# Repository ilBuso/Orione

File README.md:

# Orione

Orione is a custom 60% mechanical keyboard powered by Raspberry Pi Pico.

## Table of Contents

- [About the Project](#about-the-project)
- [Key Features](#key-features)
- [Making It Your Own](#making-it-your-own)
- [What You'll Need](#what-youll-need)
  - [Hardware Components](#hardware-components)
  - [Software Tools](#software-tools)
- [The PCB](#the-pcb)
- [The Chassis](#the-chassis)
- [Project layout](#project-layout)
- [Video and Presentation](#video-and-presentation)
- [The Team](#the-team)

## About the Project

The need for a keyboard with a rotary encoder that could be customized without compromising on functionality sparked the creation of this project. When existing options fell short of meeting these requirements, Orione was born: a custom 60% mechanical keyboard powered by the Raspberry Pi Pico, featuring fully customizable firmware and a dual-layer system that packs maximum functionality into a minimal footprint.

Orione is built around the compact 60% keyboard layout, which strips away the function row and number pad to create a more ergonomic typing experience. At its heart is the Raspberry Pi Pico microcontroller, an affordable and reliable brain that handles everything from key presses to USB communication.

What makes Orione special is its programmable dual-layer system. Through a dedicated function key, you can access an entirely separate layer of key functions, meaning you don't lose any functionality despite the smaller form factor. It's like having two keyboards in one compact package.

## Key Features

The design philosophy behind Orione was simple: create something that feels personal and works exactly the way I want it to. Here's what that translated into:

The **60% layout** keeps everything within easy reach, no more stretching for distant keys or function rows. A **dual-layer system** accessed through a dedicated function key means I haven't sacrificed any functionality for compactness.

The **rotary encoder** handles volume control beautifully, with raise, lower, and mute functionality at your fingertips. There's also a **Caps Lock LED indicator** for quick visual feedback.

For switches are for the most part **Gateron Yellow switches** that provide smooth linear action for most keys, while **Gateron Blue switches** offer tactile feedback on select keys where I wanted that extra confirmation.

Most importantly, the firmware is **fully customizable**. Every key can be remapped, every function can be changed. The Raspberry Pi Pico makes this possible, and the open-source nature of the project means you're never locked into my choices.

## Making It Your Own

One of Orione's defining features is how easily you can make it yours. The firmware is completely open and modifiable. Want to change what a key does? Remap the function layer? It's all possible:

Start by editing the keymap configuration files to match your preferences. Once you're happy with your changes, recompile the firmware and flash it to your Raspberry Pi Pico. That's it, you've got a personalized keyboard that works exactly the way you want it to.

## What You'll Need

### Hardware Components

Building Orione requires a carefully selected set of components. You'll need a **Raspberry Pi Pico** as the microcontroller, it's the brain of the operation. The **rotary encoder** provides that tactile volume control I was after, while a **LED** serves as the Caps Lock indicator.s

For the switches, you'll need **62 mechanical switches** total. You'll also need a matching set of **62 keycaps** and **62 diodes** for the key matrix.

Finally, there's the **custom PCB** that I designed specifically for this project, bringing all these components together in a compact and functional layout.

### Software Tools

The development environment revolves around **VS Code**, which I used for writing and debugging the firmware. For the PCB design, **KiCad** handled both the schematics and the layout. The chassis and 3D components were modeled in **Blender**.

On the firmware side, the project uses the **Raspberry Pi Pico C/C++ SDK**, following the official _Getting Started guide_ will get you set up properly. The **TinyUSB Library** is crucial here, as it enables USB HID communication between the Pico and your computer through the micro USB port, making the keyboard actually function as, well, a keyboard.

## The PCB

## The Chassis

## Project layout

```
/
├───datasheets
|   └───...
├───firmware
│   ├───config
│   └───src
│       ├───init
│       │   ├───init.h
│       │   └───init.c
│       ├───interrupts
│       │   ├───interrupts.h
│       │   └───interrupts.c
│       ├───matrix
│       │   ├───keymap
│       │   │   ├───keymap.h
│       │   │   └───keymap.c
│       │   └───scan_rows
│       │       ├───scan_rows.h
│       │       └───scan_rows.c
│       ├───rotary_encoder
│       │   ├───rotary_encoder.h
│       │   └───rotary_encoder.c
│       └───usb
│           ├───usb_callbacks
│           │  ├───usb_callbacks.h
│           │  └───usb_callbacks.c
│           └───usb_descriptors
│              ├───usb_descriptors.h
│              └───usb_descriptors.c
├───pcb
│   └───...
└───chassis
    └───...
```

## Video and Presentation

[Video](https://youtu.be/jeuJEti2THU)

[Presentation](assets/Orione.pdf)

## The Team

In the team we collaborated closely with eachother, both in presence and through Github.

|Name|Github handle|
|---|---|
|Alessandro Busola| [@ilBuso](https://github.com/ilBuso)|
|Giulio Pimenoff Verdolin|[@Giuliopime](https://github.com/Giuliopime)|
|Michele Pezzo|[@MichelePZZ](https://github.com/MichelePZZ)|
|Daniel Biz|[@BizDaniel](https://github.com/BizDaniel)|

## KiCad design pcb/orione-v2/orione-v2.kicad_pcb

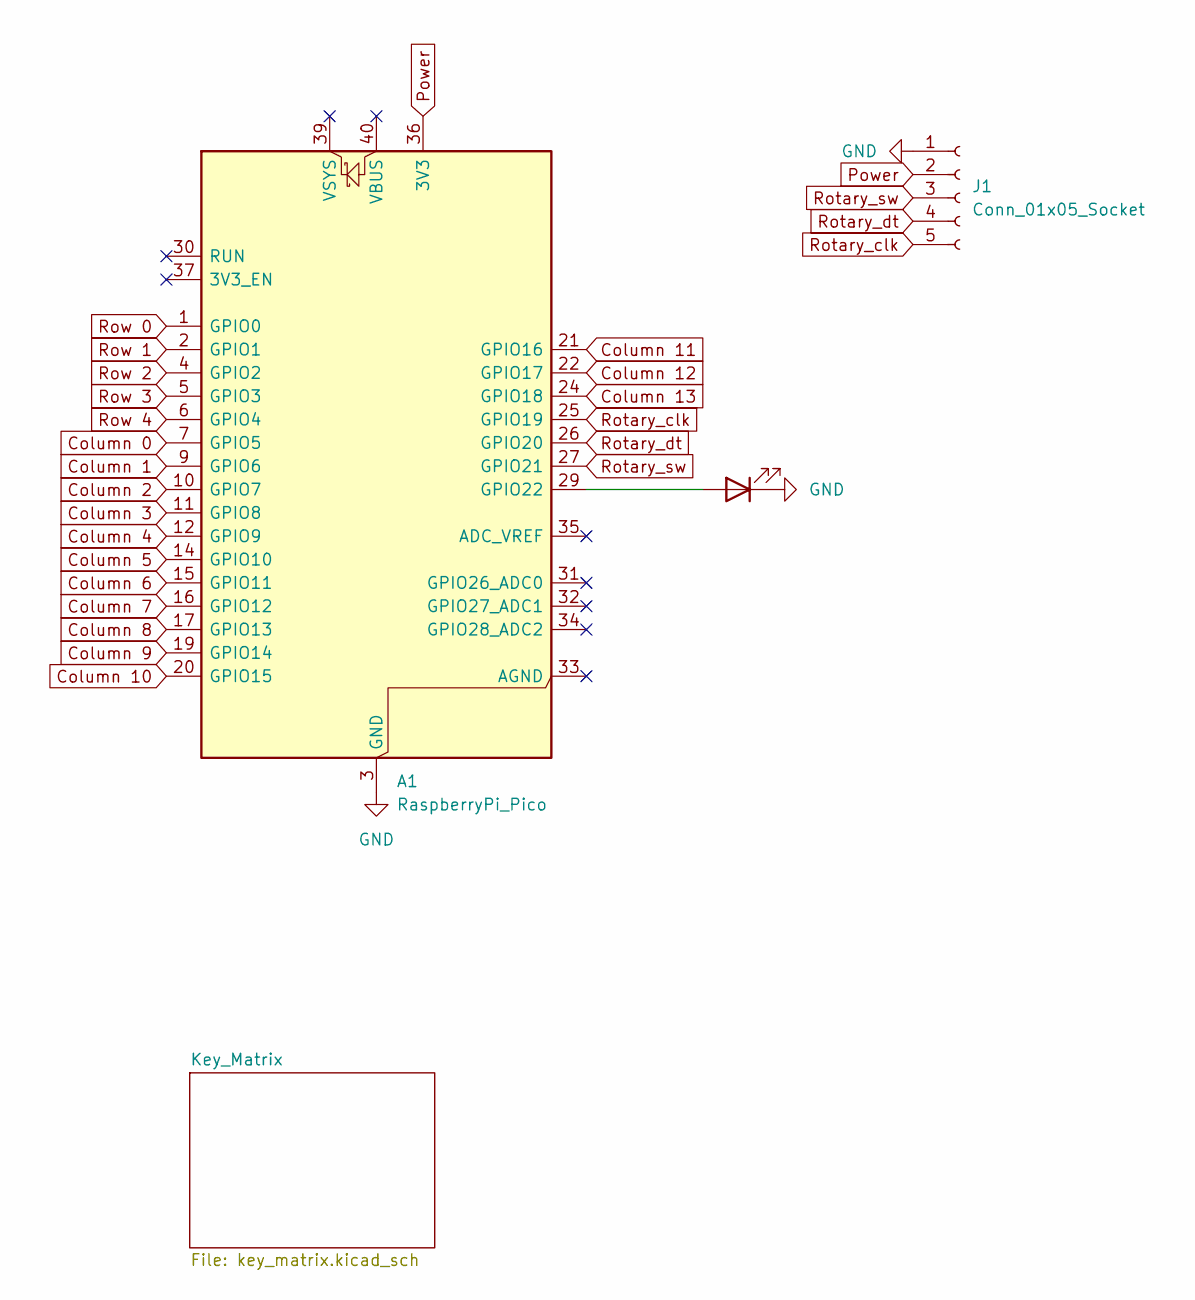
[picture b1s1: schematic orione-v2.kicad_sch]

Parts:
A1: RaspberryPi_Pico; RaspberryPi_Pico_Common_Unspecified
D63: LED; LED_D5.0mm
J1: Conn_01x05_Socket; PinSocket_1x05_P2.54mm_Vertical

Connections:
Column 0: A1.7 (GPIO5); also elsewhere on the board
Column 1: A1.9 (GPIO6); also elsewhere on the board
Column 2: A1.10 (GPIO7); also elsewhere on the board
Column 3: A1.11 (GPIO8); also elsewhere on the board
Column 4: A1.12 (GPIO9); also elsewhere on the board
Column 5: A1.14 (GPIO10); also elsewhere on the board
Column 6: A1.15 (GPIO11); also elsewhere on the board
Column 7: A1.16 (GPIO12); also elsewhere on the board
Column 8: A1.17 (GPIO13); also elsewhere on the board
Column 9: A1.19 (GPIO14); also elsewhere on the board
Column 10: A1.20 (GPIO15); also elsewhere on the board
Column 11: A1.21 (GPIO16); also elsewhere on the board
Column 12: A1.22 (GPIO17); also elsewhere on the board
Column 13: A1.24 (GPIO18); also elsewhere on the board
GND: A1.3 (GND), A1.8 (GND), A1.13 (GND), A1.18 (GND), A1.23 (GND), A1.28 (GND), A1.38 (GND), D63.1 (K), J1.1
unnamed: A1.29 (GPIO22), D63.2 (A)
Power: A1.36 (3V3), J1.2
Rotary_clk: A1.25 (GPIO19), J1.5
Rotary_dt: A1.26 (GPIO20), J1.4
Rotary_sw: A1.27 (GPIO21), J1.3
Row 0: A1.1 (GPIO0); also elsewhere on the board
Row 1: A1.2 (GPIO1); also elsewhere on the board
Row 2: A1.4 (GPIO2); also elsewhere on the board
Row 3: A1.5 (GPIO3); also elsewhere on the board
Row 4: A1.6 (GPIO4); also elsewhere on the board

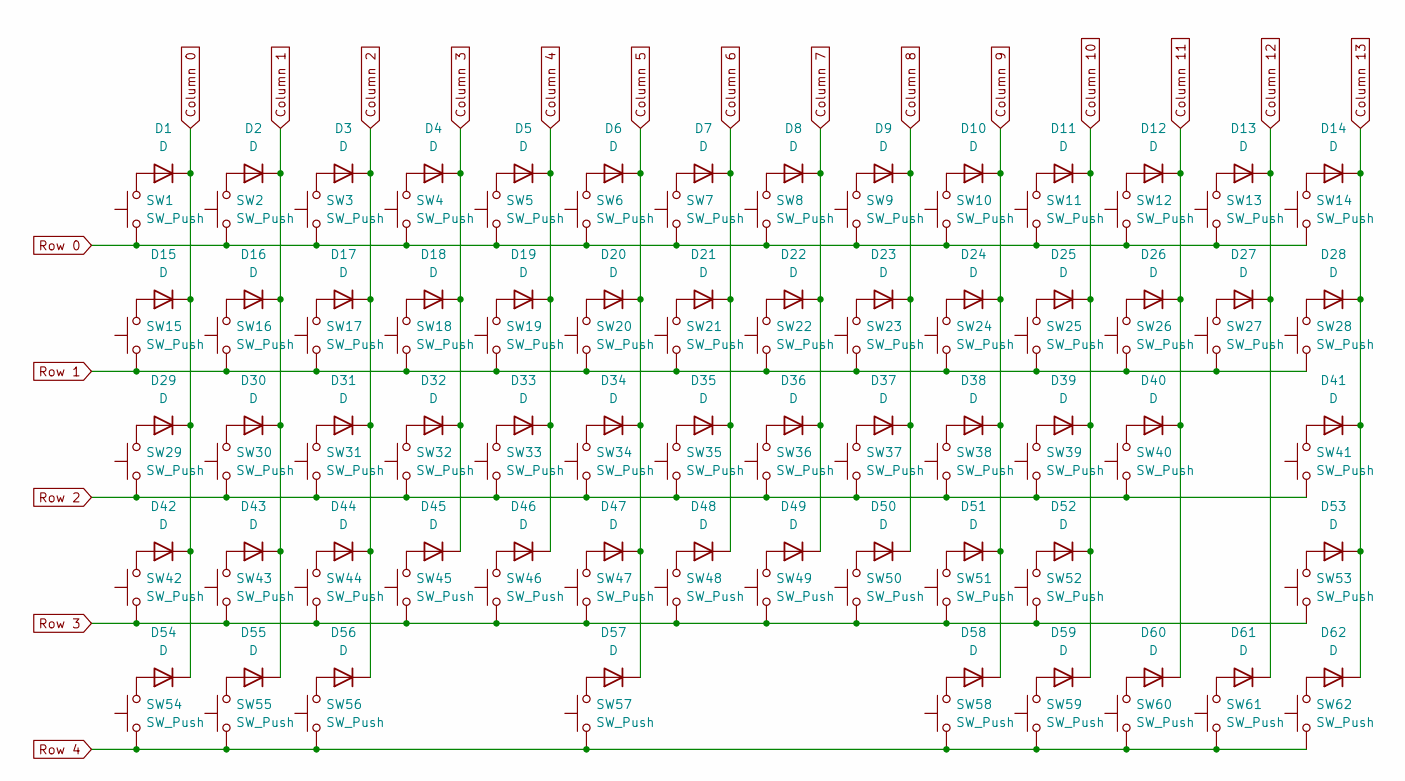
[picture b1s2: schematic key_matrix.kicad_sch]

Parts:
D1, D2, D3, D4, D5, D6, D7, D8, D9, D10, D11, D12, D13, D14, D15, D16, D17, D18, D19, D20, D21, D22, D23, D24, D25, D26, D27, D28, D29, D30, D31, D32, D33, D34, D35, D36, D37, D38, D39, D40, D41, D42, D43, D44, D45, D46, D47, D48, D49, D50, D51, D52, D53, D54, D55, D56, D57, D58, D59, D60, D61, D62: D; D_A-405_P7.62mm_Horizontal
SW1, SW2, SW3, SW4, SW5, SW6, SW7, SW8, SW9, SW10, SW11, SW12, SW13, SW16, SW17, SW18, SW19, SW20, SW21, SW22, SW23, SW24, SW25, SW26, SW27, SW30, SW31, SW32, SW33, SW34, SW35, SW36, SW37, SW38, SW39, SW40, SW43, SW44, SW45, SW46, SW47, SW48, SW49, SW50, SW51, SW52, SW58, SW59, SW60, SW61, SW62: SW_Push; SW_Cherry_MX_1.00u_PCB
SW14: SW_Push; SW_Cherry_MX_2.00u_PCB
SW15, SW28: SW_Push; SW_Cherry_MX_1.50u_PCB
SW29: SW_Push; SW_Cherry_MX_1.75u_PCB
SW41, SW42: SW_Push; SW_Cherry_MX_2.25u_PCB
SW53: SW_Push; SW_Cherry_MX_2.75u_PCB
SW54, SW55, SW56: SW_Push; SW_Cherry_MX_1.25u_PCB
SW57: SW_Push; SW_Cherry_MX_6.25u_PCB

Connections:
Column 0: D1.1 (K), D15.1 (K), D29.1 (K), D42.1 (K), D54.1 (K); also elsewhere on the board
Column 1: D2.1 (K), D16.1 (K), D30.1 (K), D43.1 (K), D55.1 (K); also elsewhere on the board
Column 2: D3.1 (K), D17.1 (K), D31.1 (K), D44.1 (K), D56.1 (K); also elsewhere on the board
Column 3: D4.1 (K), D18.1 (K), D32.1 (K), D45.1 (K); also elsewhere on the board
Column 4: D5.1 (K), D19.1 (K), D33.1 (K), D46.1 (K); also elsewhere on the board
Column 5: D6.1 (K), D20.1 (K), D34.1 (K), D47.1 (K), D57.1 (K); also elsewhere on the board
Column 6: D7.1 (K), D21.1 (K), D35.1 (K), D48.1 (K); also elsewhere on the board
Column 7: D8.1 (K), D22.1 (K), D36.1 (K), D49.1 (K); also elsewhere on the board
Column 8: D9.1 (K), D23.1 (K), D37.1 (K), D50.1 (K); also elsewhere on the board
Column 9: D10.1 (K), D24.1 (K), D38.1 (K), D51.1 (K), D58.1 (K); also elsewhere on the board
Column 10: D11.1 (K), D25.1 (K), D39.1 (K), D52.1 (K), D59.1 (K); also elsewhere on the board
Column 11: D12.1 (K), D26.1 (K), D40.1 (K), D60.1 (K); also elsewhere on the board
Column 12: D13.1 (K), D27.1 (K), D61.1 (K); also elsewhere on the board
Column 13: D14.1 (K), D28.1 (K), D41.1 (K), D53.1 (K), D62.1 (K); also elsewhere on the board
unnamed: D1.2 (A), SW1.2
unnamed: D2.2 (A), SW2.2
unnamed: D3.2 (A), SW3.2
unnamed: D4.2 (A), SW4.2
unnamed: D5.2 (A), SW5.2
unnamed: D6.2 (A), SW6.2
unnamed: D7.2 (A), SW7.2
unnamed: D8.2 (A), SW8.2
unnamed: D9.2 (A), SW9.2
unnamed: D10.2 (A), SW10.2
unnamed: D11.2 (A), SW11.2
unnamed: D12.2 (A), SW12.2
unnamed: D13.2 (A), SW13.2
unnamed: D14.2 (A), SW14.2
unnamed: D15.2 (A), SW15.2
unnamed: D16.2 (A), SW16.2
unnamed: D17.2 (A), SW17.2
unnamed: D18.2 (A), SW18.2
unnamed: D19.2 (A), SW19.2
unnamed: D20.2 (A), SW20.2
unnamed: D21.2 (A), SW21.2
unnamed: D22.2 (A), SW22.2
unnamed: D23.2 (A), SW23.2
unnamed: D24.2 (A), SW24.2
unnamed: D25.2 (A), SW25.2
unnamed: D26.2 (A), SW26.2
unnamed: D27.2 (A), SW27.2
unnamed: D28.2 (A), SW28.2
unnamed: D29.2 (A), SW29.2
unnamed: D30.2 (A), SW30.2
unnamed: D31.2 (A), SW31.2
unnamed: D32.2 (A), SW32.2
unnamed: D33.2 (A), SW33.2
unnamed: D34.2 (A), SW34.2
unnamed: D35.2 (A), SW35.2
unnamed: D36.2 (A), SW36.2
unnamed: D37.2 (A), SW37.2
unnamed: D38.2 (A), SW38.2
unnamed: D39.2 (A), SW39.2
unnamed: D40.2 (A), SW40.2
unnamed: D41.2 (A), SW41.2
unnamed: D42.2 (A), SW42.2
unnamed: D43.2 (A), SW43.2
unnamed: D44.2 (A), SW44.2
unnamed: D45.2 (A), SW45.2
unnamed: D46.2 (A), SW46.2
unnamed: D47.2 (A), SW47.2
unnamed: D48.2 (A), SW48.2
unnamed: D49.2 (A), SW49.2
unnamed: D50.2 (A), SW50.2
unnamed: D51.2 (A), SW51.2
unnamed: D52.2 (A), SW52.2
unnamed: D53.2 (A), SW53.2
unnamed: D54.2 (A), SW54.2
unnamed: D55.2 (A), SW55.2
unnamed: D56.2 (A), SW56.2
unnamed: D57.2 (A), SW57.2
unnamed: D58.2 (A), SW58.2
unnamed: D59.2 (A), SW59.2
unnamed: D60.2 (A), SW60.2
unnamed: D61.2 (A), SW61.2
unnamed: D62.2 (A), SW62.2
Row 0: SW1.1, SW2.1, SW3.1, SW4.1, SW5.1, SW6.1, SW7.1, SW8.1, SW9.1, SW10.1, SW11.1, SW12.1, SW13.1, SW14.1; also elsewhere on the board
Row 1: SW15.1, SW16.1, SW17.1, SW18.1, SW19.1, SW20.1, SW21.1, SW22.1, SW23.1, SW24.1, SW25.1, SW26.1, SW27.1, SW28.1; also elsewhere on the board
Row 2: SW29.1, SW30.1, SW31.1, SW32.1, SW33.1, SW34.1, SW35.1, SW36.1, SW37.1, SW38.1, SW39.1, SW40.1, SW41.1; also elsewhere on the board
Row 3: SW42.1, SW43.1, SW44.1, SW45.1, SW46.1, SW47.1, SW48.1, SW49.1, SW50.1, SW51.1, SW52.1, SW53.1; also elsewhere on the board
Row 4: SW54.1, SW55.1, SW56.1, SW57.1, SW58.1, SW59.1, SW60.1, SW61.1, SW62.1; also elsewhere on the board

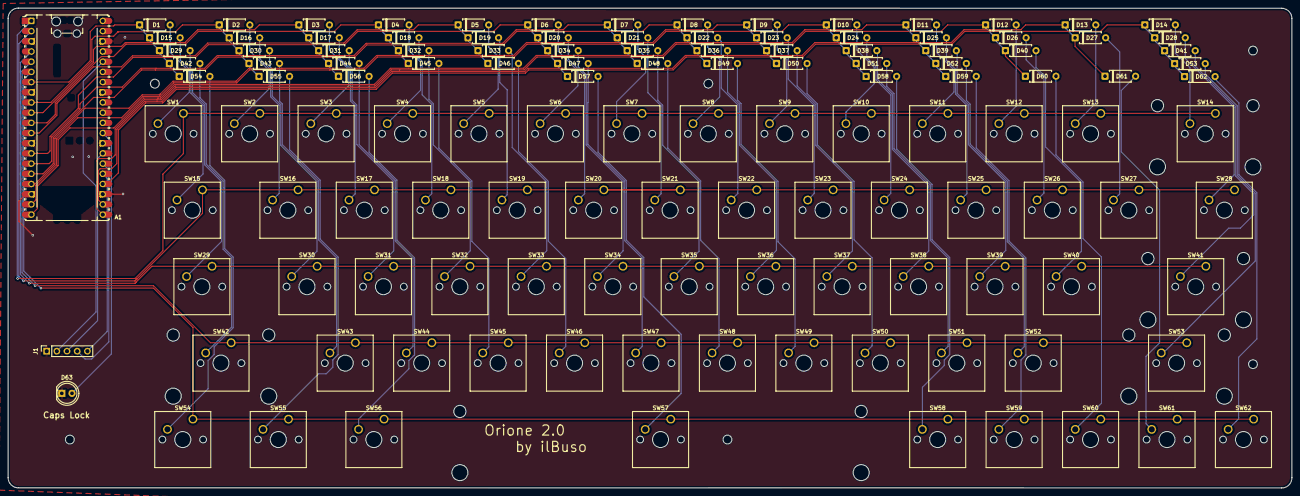
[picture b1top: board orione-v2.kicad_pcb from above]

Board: 2 copper layers, 319.9 x 119.6 mm, 127 parts (0 on the bottom side), 87 nets.

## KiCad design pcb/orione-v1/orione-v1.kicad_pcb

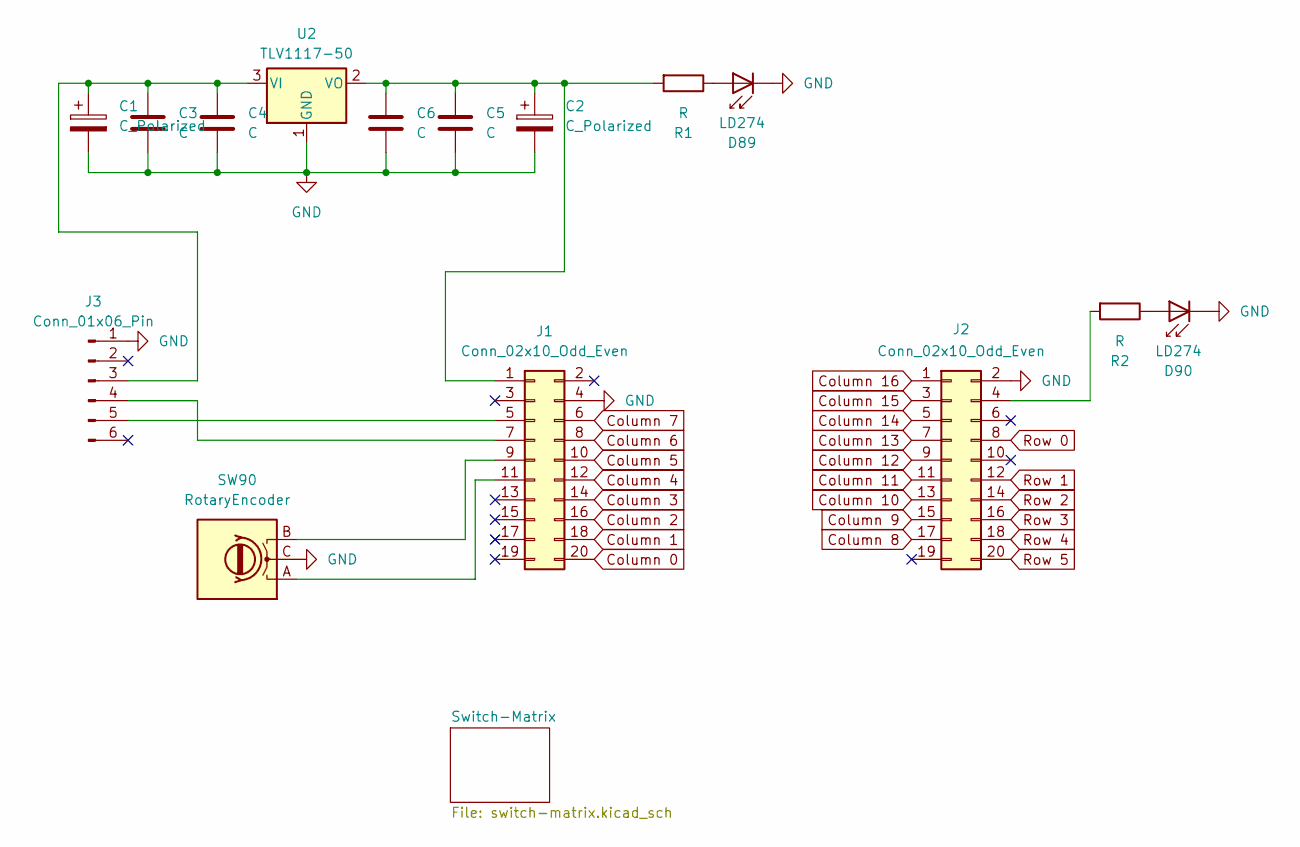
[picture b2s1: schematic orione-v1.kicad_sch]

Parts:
C1, C2: C_Polarized; CP_Radial_Tantal_D4.5mm_P5.00mm
C3, C4, C5, C6: C; C_Radial_D4.0mm_H7.0mm_P1.50mm
D89, D90: LD274; LED_D5.0mm_IRGrey
J1, J2: Conn_02x10_Odd_Even; PinHeader_2x10_P2.54mm_Vertical
J3: Conn_01x06_Pin; PinHeader_1x06_P2.54mm_Horizontal
R1, R2: R; R_Axial_DIN0207_L6.3mm_D2.5mm_P10.16mm_Horizontal
SW90: RotaryEncoder; RotaryEncoder_Alps_EC12E_Vertical_H20mm
U2: TLV1117-50; TO-220-3_Vertical

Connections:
Column 0: J1.20; also elsewhere on the board
Column 1: J1.18; also elsewhere on the board
Column 2: J1.16; also elsewhere on the board
Column 3: J1.14; also elsewhere on the board
Column 4: J1.12; also elsewhere on the board
Column 5: J1.10; also elsewhere on the board
Column 6: J1.8; also elsewhere on the board
Column 7: J1.6; also elsewhere on the board
Column 8: J2.17; also elsewhere on the board
Column 9: J2.15; also elsewhere on the board
Column 10: J2.13; also elsewhere on the board
Column 11: J2.11; also elsewhere on the board
Column 12: J2.9; also elsewhere on the board
Column 13: J2.7; also elsewhere on the board
Column 14: J2.5; also elsewhere on the board
Column 15: J2.3; also elsewhere on the board
Column 16: J2.1; also elsewhere on the board
GND: C1.2, C2.2, C3.2, C4.2, C5.2, C6.2, D89.1 (K), D90.1 (K), J1.4, J2.2, J3.1, SW90.C, U2.1 (GND)
unnamed: D89.2 (A), R1.1
unnamed: D90.2 (A), R2.1
unnamed: C2.1, C5.1, C6.1, J1.1, R1.2, U2.2 (VO)
unnamed: J1.5, J3.5
unnamed: J1.7, J3.4
unnamed: J1.9, SW90.B
unnamed: J1.11, SW90.A
unnamed: J2.4, R2.2
unnamed: C1.1, C3.1, C4.1, J3.3, U2.3 (VI)
Row 0: J2.8; also elsewhere on the board
Row 1: J2.12; also elsewhere on the board
Row 2: J2.14; also elsewhere on the board
Row 3: J2.16; also elsewhere on the board
Row 4: J2.18; also elsewhere on the board
Row 5: J2.20; also elsewhere on the board

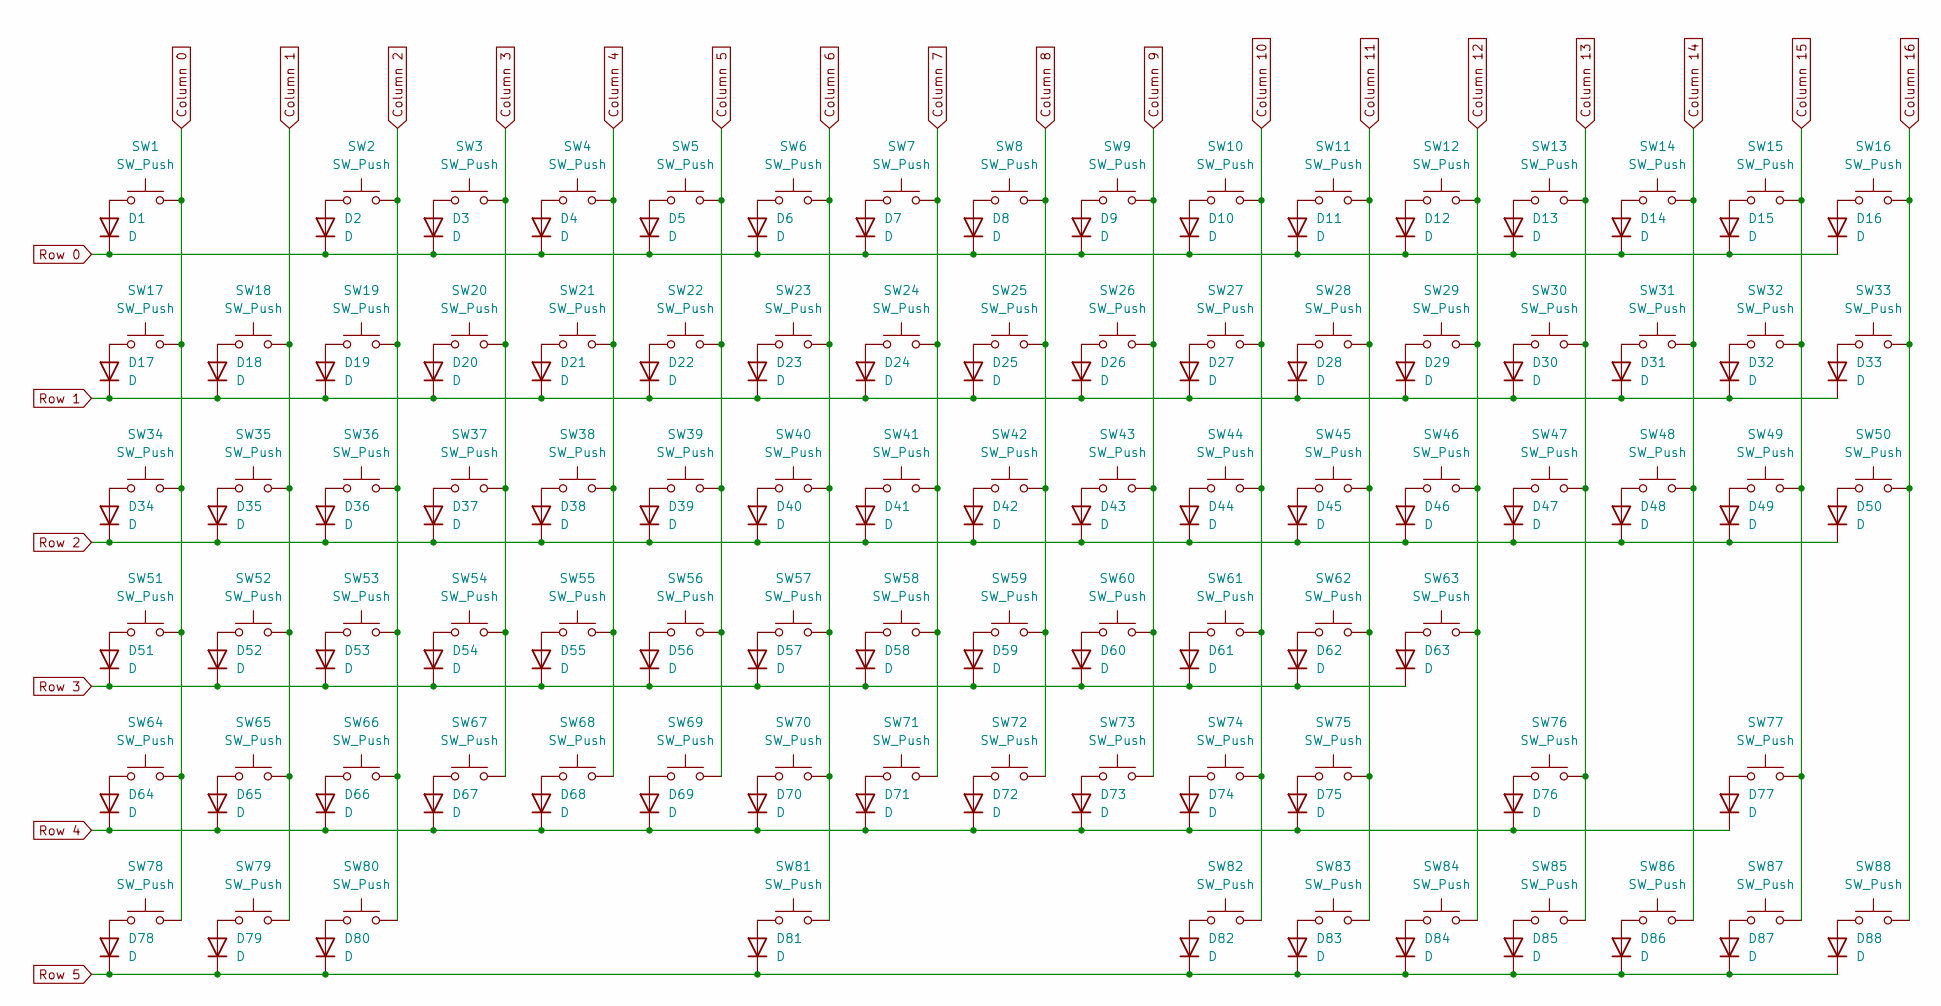
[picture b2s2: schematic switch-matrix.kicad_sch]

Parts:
D1, D2, D3, D4, D5, D6, D7, D8, D9, D10, D11, D12, D13, D14, D15, D16, D17, D18, D19, D20, D21, D22, D23, D24, D25, D26, D27, D28, D29, D30, D31, D32, D33, D34, D35, D36, D37, D38, D39, D40, D41, D42, D43, D44, D45, D46, D47, D48, D49, D50, D51, D52, D53, D54, D55, D56, D57, D58, D59, D60, D61, D62, D63, D64, D65, D66, D67, D68, D69, D70, D71, D72, D73, D74, D75, D76, D77, D78, D79, D80, D81, D82, D83, D84, D85, D86, D87, D88: D; R_Axial_DIN0204_L3.6mm_D1.6mm_P5.08mm_Horizontal
SW1, SW2, SW3, SW4, SW5, SW6, SW7, SW8, SW9, SW10, SW11, SW12, SW13, SW14, SW15, SW16, SW17, SW18, SW19, SW20, SW21, SW22, SW23, SW24, SW25, SW26, SW27, SW28, SW29, SW31, SW32, SW33, SW35, SW36, SW37, SW38, SW39, SW40, SW41, SW42, SW43, SW44, SW45, SW46, SW48, SW49, SW50, SW52, SW53, SW54, SW55, SW56, SW57, SW58, SW59, SW60, SW61, SW62, SW63, SW65, SW66, SW67, SW68, SW69, SW70, SW71, SW72, SW73, SW74, SW75, SW77, SW86, SW87, SW88: SW_Push; SW_Cherry_MX_1.00u_PCB
SW30: SW_Push; SW_Cherry_MX_2.00u_PCB
SW34: SW_Push; SW_Cherry_MX_1.50u_PCB
SW47: SW_Push; SW_Cherry_MX_ISOEnter_PCB
SW51: SW_Push; SW_Cherry_MX_1.75u_PCB
SW64, SW78, SW79, SW80, SW82, SW83, SW84, SW85: SW_Push; SW_Cherry_MX_1.25u_PCB
SW76: SW_Push; SW_Cherry_MX_2.75u_PCB
SW81: SW_Push; SW_Cherry_MX_6.25u_PCB

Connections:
Column 0: SW1.2, SW17.2, SW34.2, SW51.2, SW64.2, SW78.2; also elsewhere on the board
Column 1: SW18.2, SW35.2, SW52.2, SW65.2, SW79.2; also elsewhere on the board
Column 2: SW2.2, SW19.2, SW36.2, SW53.2, SW66.2, SW80.2; also elsewhere on the board
Column 3: SW3.2, SW20.2, SW37.2, SW54.2, SW67.2; also elsewhere on the board
Column 4: SW4.2, SW21.2, SW38.2, SW55.2, SW68.2; also elsewhere on the board
Column 5: SW5.2, SW22.2, SW39.2, SW56.2, SW69.2; also elsewhere on the board
Column 6: SW6.2, SW23.2, SW40.2, SW57.2, SW70.2, SW81.2; also elsewhere on the board
Column 7: SW7.2, SW24.2, SW41.2, SW58.2, SW71.2; also elsewhere on the board
Column 8: SW8.2, SW25.2, SW42.2, SW59.2, SW72.2; also elsewhere on the board
Column 9: SW9.2, SW26.2, SW43.2, SW60.2, SW73.2; also elsewhere on the board
Column 10: SW10.2, SW27.2, SW44.2, SW61.2, SW74.2, SW82.2; also elsewhere on the board
Column 11: SW11.2, SW28.2, SW45.2, SW62.2, SW75.2, SW83.2; also elsewhere on the board
Column 12: SW12.2, SW29.2, SW46.2, SW63.2, SW84.2; also elsewhere on the board
Column 13: SW13.2, SW30.2, SW47.2, SW76.2, SW85.2; also elsewhere on the board
Column 14: SW14.2, SW31.2, SW48.2, SW86.2; also elsewhere on the board
Column 15: SW15.2, SW32.2, SW49.2, SW77.2, SW87.2; also elsewhere on the board
Column 16: SW16.2, SW33.2, SW50.2, SW88.2; also elsewhere on the board
unnamed: D1.2 (A), SW1.1
unnamed: D2.2 (A), SW2.1
unnamed: D3.2 (A), SW3.1
unnamed: D4.2 (A), SW4.1
unnamed: D5.2 (A), SW5.1
unnamed: D6.2 (A), SW6.1
unnamed: D7.2 (A), SW7.1
unnamed: D8.2 (A), SW8.1
unnamed: D9.2 (A), SW9.1
unnamed: D10.2 (A), SW10.1
unnamed: D11.2 (A), SW11.1
unnamed: D12.2 (A), SW12.1
unnamed: D13.2 (A), SW13.1
unnamed: D14.2 (A), SW14.1
unnamed: D15.2 (A), SW15.1
unnamed: D16.2 (A), SW16.1
unnamed: D17.2 (A), SW17.1
unnamed: D18.2 (A), SW18.1
unnamed: D19.2 (A), SW19.1
unnamed: D20.2 (A), SW20.1
unnamed: D21.2 (A), SW21.1
unnamed: D22.2 (A), SW22.1
unnamed: D23.2 (A), SW23.1
unnamed: D24.2 (A), SW24.1
unnamed: D25.2 (A), SW25.1
unnamed: D26.2 (A), SW26.1
unnamed: D27.2 (A), SW27.1
unnamed: D28.2 (A), SW28.1
unnamed: D29.2 (A), SW29.1
unnamed: D30.2 (A), SW30.1
unnamed: D31.2 (A), SW31.1
unnamed: D32.2 (A), SW32.1
unnamed: D33.2 (A), SW33.1
unnamed: D34.2 (A), SW34.1
unnamed: D35.2 (A), SW35.1
unnamed: D36.2 (A), SW36.1
unnamed: D37.2 (A), SW37.1
unnamed: D38.2 (A), SW38.1
unnamed: D39.2 (A), SW39.1
unnamed: D40.2 (A), SW40.1
unnamed: D41.2 (A), SW41.1
unnamed: D42.2 (A), SW42.1
unnamed: D43.2 (A), SW43.1
unnamed: D44.2 (A), SW44.1
unnamed: D45.2 (A), SW45.1
unnamed: D46.2 (A), SW46.1
unnamed: D47.2 (A), SW47.1
unnamed: D48.2 (A), SW48.1
unnamed: D49.2 (A), SW49.1
unnamed: D50.2 (A), SW50.1
unnamed: D51.2 (A), SW51.1
unnamed: D52.2 (A), SW52.1
unnamed: D53.2 (A), SW53.1
unnamed: D54.2 (A), SW54.1
unnamed: D55.2 (A), SW55.1
unnamed: D56.2 (A), SW56.1
unnamed: D57.2 (A), SW57.1
unnamed: D58.2 (A), SW58.1
unnamed: D59.2 (A), SW59.1
unnamed: D60.2 (A), SW60.1
unnamed: D61.2 (A), SW61.1
unnamed: D62.2 (A), SW62.1
unnamed: D63.2 (A), SW63.1
unnamed: D64.2 (A), SW64.1
unnamed: D65.2 (A), SW65.1
unnamed: D66.2 (A), SW66.1
unnamed: D67.2 (A), SW67.1
unnamed: D68.2 (A), SW68.1
unnamed: D69.2 (A), SW69.1
unnamed: D70.2 (A), SW70.1
unnamed: D71.2 (A), SW71.1
unnamed: D72.2 (A), SW72.1
unnamed: D73.2 (A), SW73.1
unnamed: D74.2 (A), SW74.1
unnamed: D75.2 (A), SW75.1
unnamed: D76.2 (A), SW76.1
unnamed: D77.2 (A), SW77.1
unnamed: D78.2 (A), SW78.1
unnamed: D79.2 (A), SW79.1
unnamed: D80.2 (A), SW80.1
unnamed: D81.2 (A), SW81.1
unnamed: D82.2 (A), SW82.1
unnamed: D83.2 (A), SW83.1
unnamed: D84.2 (A), SW84.1
unnamed: D85.2 (A), SW85.1
unnamed: D86.2 (A), SW86.1
unnamed: D87.2 (A), SW87.1
unnamed: D88.2 (A), SW88.1
Row 0: D1.1 (K), D2.1 (K), D3.1 (K), D4.1 (K), D5.1 (K), D6.1 (K), D7.1 (K), D8.1 (K), D9.1 (K), D10.1 (K), D11.1 (K), D12.1 (K), D13.1 (K), D14.1 (K), D15.1 (K), D16.1 (K); also elsewhere on the board
Row 1: D17.1 (K), D18.1 (K), D19.1 (K), D20.1 (K), D21.1 (K), D22.1 (K), D23.1 (K), D24.1 (K), D25.1 (K), D26.1 (K), D27.1 (K), D28.1 (K), D29.1 (K), D30.1 (K), D31.1 (K), D32.1 (K), D33.1 (K); also elsewhere on the board
Row 2: D34.1 (K), D35.1 (K), D36.1 (K), D37.1 (K), D38.1 (K), D39.1 (K), D40.1 (K), D41.1 (K), D42.1 (K), D43.1 (K), D44.1 (K), D45.1 (K), D46.1 (K), D47.1 (K), D48.1 (K), D49.1 (K), D50.1 (K); also elsewhere on the board
Row 3: D51.1 (K), D52.1 (K), D53.1 (K), D54.1 (K), D55.1 (K), D56.1 (K), D57.1 (K), D58.1 (K), D59.1 (K), D60.1 (K), D61.1 (K), D62.1 (K), D63.1 (K); also elsewhere on the board
Row 4: D64.1 (K), D65.1 (K), D66.1 (K), D67.1 (K), D68.1 (K), D69.1 (K), D70.1 (K), D71.1 (K), D72.1 (K), D73.1 (K), D74.1 (K), D75.1 (K), D76.1 (K), D77.1 (K); also elsewhere on the board
Row 5: D78.1 (K), D79.1 (K), D80.1 (K), D81.1 (K), D82.1 (K), D83.1 (K), D84.1 (K), D85.1 (K), D86.1 (K), D87.1 (K), D88.1 (K); also elsewhere on the board

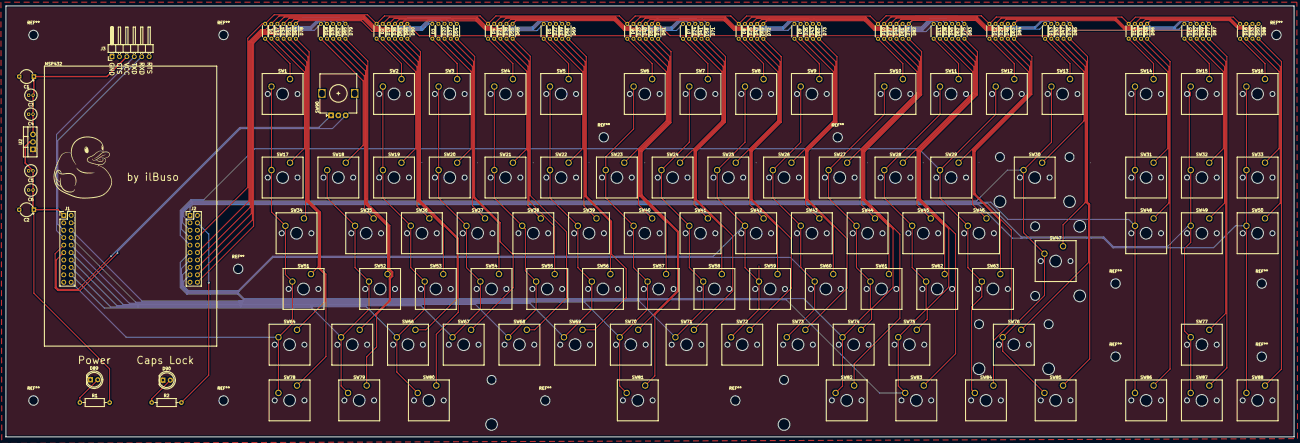
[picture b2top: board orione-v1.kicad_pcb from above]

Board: 2 copper layers, 440.5 x 147.4 mm, 191 parts (0 on the bottom side), 121 nets.

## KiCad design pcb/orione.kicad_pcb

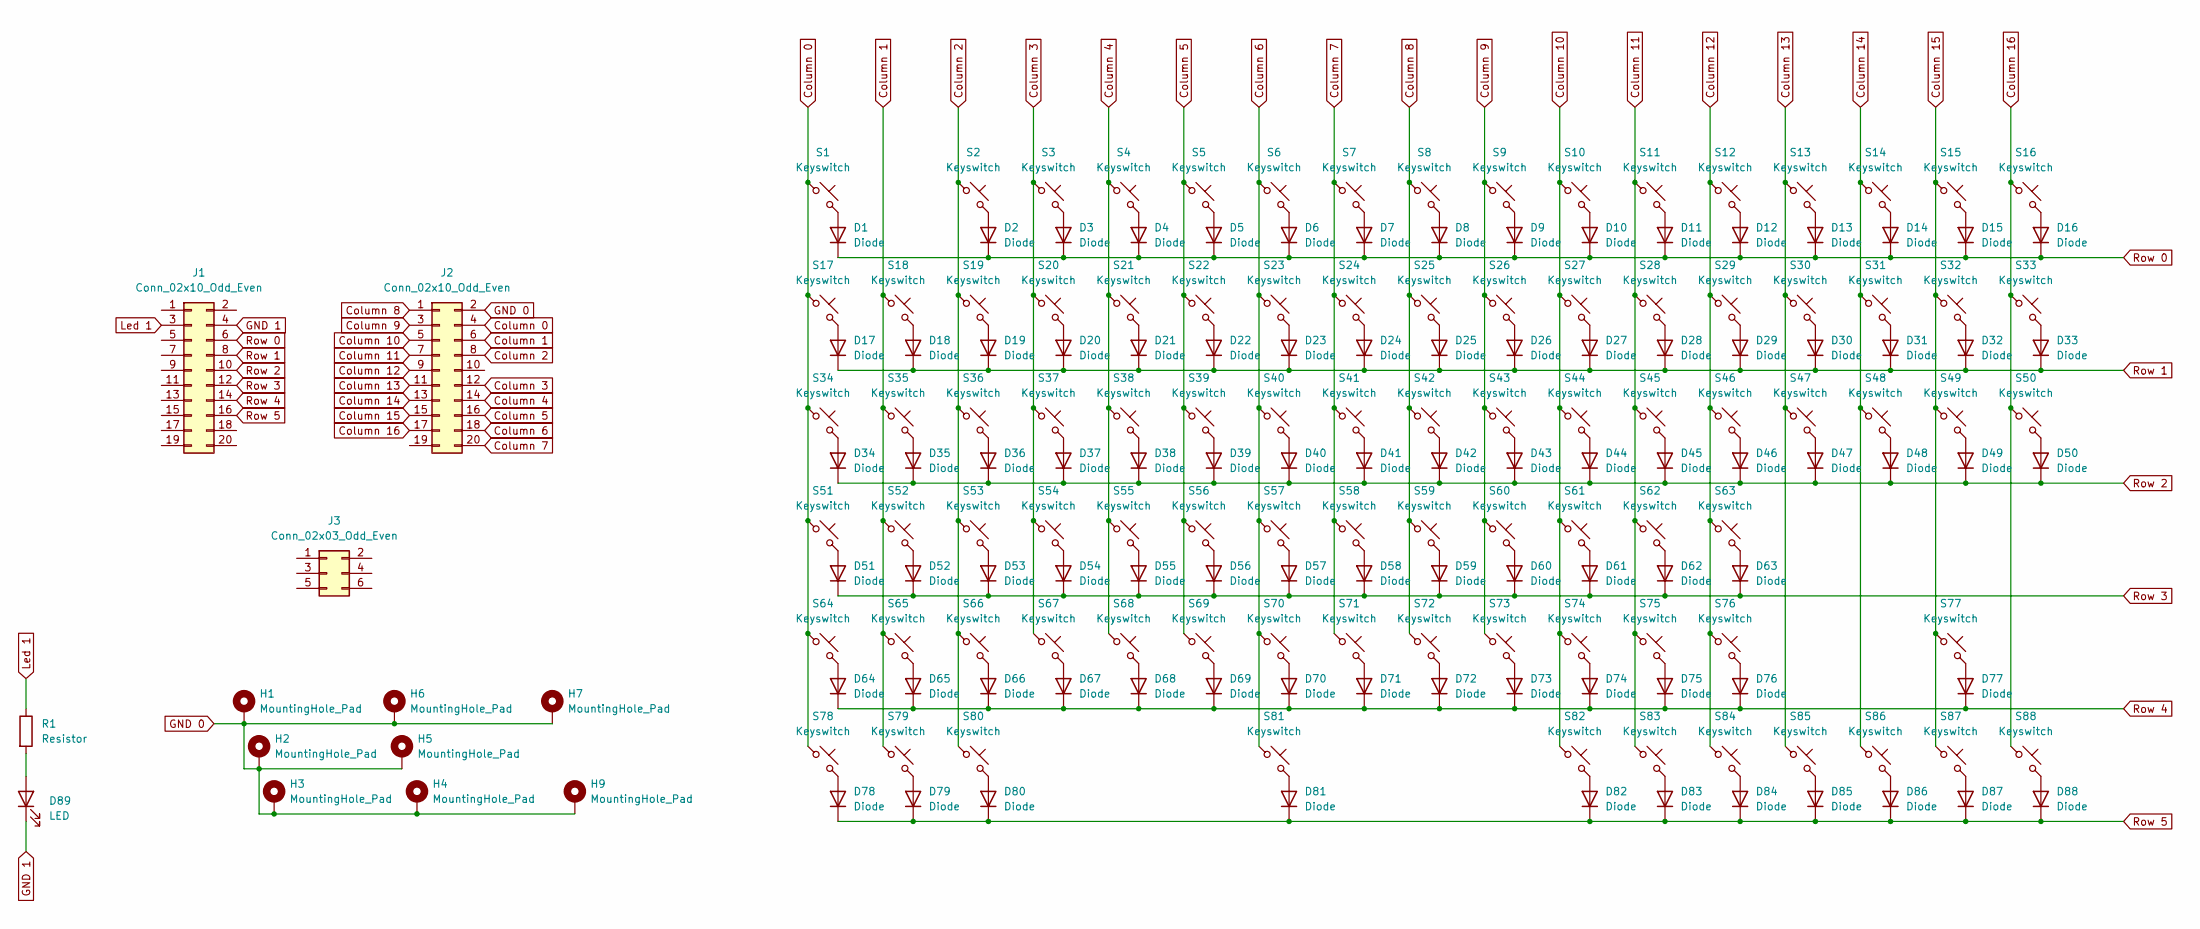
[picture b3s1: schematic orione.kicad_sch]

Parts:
D1, D2, D3, D4, D5, D6, D7, D8, D9, D10, D11, D12, D13, D14, D15, D16, D17, D18, D19, D20, D21, D22, D23, D24, D25, D26, D27, D28, D29, D30, D31, D32, D33, D34, D35, D36, D37, D38, D39, D40, D41, D42, D43, D44, D45, D46, D47, D48, D49, D50, D51, D52, D53, D54, D55, D56, D57, D58, D59, D60, D61, D62, D63, D64, D65, D66, D67, D68, D69, D70, D71, D72, D73, D74, D75, D76, D77, D78, D79, D80, D81, D82, D83, D84, D85, D86, D87, D88: Diode; Diode_DO-35
D89: LED; LED_D5.0mm
H1, H2, H3, H4, H5, H6, H7, H9: MountingHole_Pad; MountingHole_3.2mm_M3_Pad_Via
J1, J2: Conn_02x10_Odd_Even; PinHeader_2x10_P2.54mm_Vertical
J3: Conn_02x03_Odd_Even; PinHeader_2x03_P2.54mm_Horizontal
R1: Resistor; R_Axial_DIN0207_L6.3mm_D2.5mm_P10.16mm_Horizontal
S1, S2, S3, S4, S5, S6, S7, S8, S9, S10, S11, S12, S13, S14, S15, S16, S17, S18, S19, S20, S21, S22, S23, S24, S25, S26, S27, S28, S29, S30, S31, S32, S33, S34, S35, S36, S37, S38, S39, S40, S41, S42, S43, S44, S45, S46, S47, S48, S49, S50, S51, S52, S53, S54, S55, S56, S57, S58, S59, S60, S61, S62, S63, S64, S65, S66, S67, S68, S69, S70, S71, S72, S73, S74, S75, S76, S77, S78, S79, S80, S81, S82, S83, S84, S85, S86, S87, S88: Keyswitch; MX_PCB_1.00u

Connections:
Column 0: J2.4, S1.1, S17.1, S34.1, S51.1, S64.1, S78.1
Column 1: J2.6, S18.1, S35.1, S52.1, S65.1, S79.1
Column 2: J2.8, S2.1, S19.1, S36.1, S53.1, S66.1, S80.1
Column 3: J2.12, S3.1, S20.1, S37.1, S54.1, S67.1
Column 4: J2.14, S4.1, S21.1, S38.1, S55.1, S68.1
Column 5: J2.16, S5.1, S22.1, S39.1, S56.1, S69.1
Column 6: J2.18, S6.1, S23.1, S40.1, S57.1, S70.1, S81.1
Column 7: J2.20, S7.1, S24.1, S41.1, S58.1, S71.1
Column 8: J2.1, S8.1, S25.1, S42.1, S59.1, S72.1
Column 9: J2.3, S9.1, S26.1, S43.1, S60.1, S73.1
Column 10: J2.5, S10.1, S27.1, S44.1, S61.1, S74.1, S82.1
Column 11: J2.7, S11.1, S28.1, S45.1, S62.1, S75.1, S83.1
Column 12: J2.9, S12.1, S29.1, S46.1, S63.1, S76.1, S84.1
Column 13: J2.11, S13.1, S30.1, S47.1, S85.1
Column 14: J2.13, S14.1, S31.1, S48.1, S86.1
Column 15: J2.15, S15.1, S32.1, S49.1, S77.1, S87.1
Column 16: J2.17, S16.1, S33.1, S50.1, S88.1
GND 0: H1.1, H2.1, H3.1, H4.1, H5.1, H6.1, H7.1, H9.1, J2.2
GND 1: D89.1 (K), J1.4; also elsewhere on the board
Led 1: J1.3, R1.1; also elsewhere on the board
unnamed: D1.2 (A), S1.2
unnamed: D2.2 (A), S2.2
unnamed: D3.2 (A), S3.2
unnamed: D4.2 (A), S4.2
unnamed: D5.2 (A), S5.2
unnamed: D6.2 (A), S6.2
unnamed: D7.2 (A), S7.2
unnamed: D8.2 (A), S8.2
unnamed: D9.2 (A), S9.2
unnamed: D10.2 (A), S10.2
unnamed: D11.2 (A), S11.2
unnamed: D12.2 (A), S12.2
unnamed: D13.2 (A), S13.2
unnamed: D14.2 (A), S14.2
unnamed: D15.2 (A), S15.2
unnamed: D16.2 (A), S16.2
unnamed: D17.2 (A), S17.2
unnamed: D18.2 (A), S18.2
unnamed: D19.2 (A), S19.2
unnamed: D20.2 (A), S20.2
unnamed: D21.2 (A), S21.2
unnamed: D22.2 (A), S22.2
unnamed: D23.2 (A), S23.2
unnamed: D24.2 (A), S24.2
unnamed: D25.2 (A), S25.2
unnamed: D26.2 (A), S26.2
unnamed: D27.2 (A), S27.2
unnamed: D28.2 (A), S28.2
unnamed: D29.2 (A), S29.2
unnamed: D30.2 (A), S30.2
unnamed: D31.2 (A), S31.2
unnamed: D32.2 (A), S32.2
unnamed: D33.2 (A), S33.2
unnamed: D34.2 (A), S34.2
unnamed: D35.2 (A), S35.2
unnamed: D36.2 (A), S36.2
unnamed: D37.2 (A), S37.2
unnamed: D38.2 (A), S38.2
unnamed: D39.2 (A), S39.2
unnamed: D40.2 (A), S40.2
unnamed: D41.2 (A), S41.2
unnamed: D42.2 (A), S42.2
unnamed: D43.2 (A), S43.2
unnamed: D44.2 (A), S44.2
unnamed: D45.2 (A), S45.2
unnamed: D46.2 (A), S46.2
unnamed: D47.2 (A), S47.2
unnamed: D48.2 (A), S48.2
unnamed: D49.2 (A), S49.2
unnamed: D50.2 (A), S50.2
unnamed: D51.2 (A), S51.2
unnamed: D52.2 (A), S52.2
unnamed: D53.2 (A), S53.2
unnamed: D54.2 (A), S54.2
unnamed: D55.2 (A), S55.2
unnamed: D56.2 (A), S56.2
unnamed: D57.2 (A), S57.2
unnamed: D58.2 (A), S58.2
unnamed: D59.2 (A), S59.2
unnamed: D60.2 (A), S60.2
unnamed: D61.2 (A), S61.2
unnamed: D62.2 (A), S62.2
unnamed: D63.2 (A), S63.2
unnamed: D64.2 (A), S64.2
unnamed: D65.2 (A), S65.2
unnamed: D66.2 (A), S66.2
unnamed: D67.2 (A), S67.2
unnamed: D68.2 (A), S68.2
unnamed: D69.2 (A), S69.2
unnamed: D70.2 (A), S70.2
unnamed: D71.2 (A), S71.2
unnamed: D72.2 (A), S72.2
unnamed: D73.2 (A), S73.2
unnamed: D74.2 (A), S74.2
unnamed: D75.2 (A), S75.2
unnamed: D76.2 (A), S76.2
unnamed: D77.2 (A), S77.2
unnamed: D78.2 (A), S78.2
unnamed: D79.2 (A), S79.2
unnamed: D80.2 (A), S80.2
unnamed: D81.2 (A), S81.2
unnamed: D82.2 (A), S82.2
unnamed: D83.2 (A), S83.2
unnamed: D84.2 (A), S84.2
unnamed: D85.2 (A), S85.2
unnamed: D86.2 (A), S86.2
unnamed: D87.2 (A), S87.2
unnamed: D88.2 (A), S88.2
unnamed 108: D89.2 (A), R1.2; also elsewhere on the board
Row 0: D1.1 (K), D2.1 (K), D3.1 (K), D4.1 (K), D5.1 (K), D6.1 (K), D7.1 (K), D8.1 (K), D9.1 (K), D10.1 (K), D11.1 (K), D12.1 (K), D13.1 (K), D14.1 (K), D15.1 (K), D16.1 (K), J1.6
Row 1: D17.1 (K), D18.1 (K), D19.1 (K), D20.1 (K), D21.1 (K), D22.1 (K), D23.1 (K), D24.1 (K), D25.1 (K), D26.1 (K), D27.1 (K), D28.1 (K), D29.1 (K), D30.1 (K), D31.1 (K), D32.1 (K), D33.1 (K), J1.8
Row 2: D34.1 (K), D35.1 (K), D36.1 (K), D37.1 (K), D38.1 (K), D39.1 (K), D40.1 (K), D41.1 (K), D42.1 (K), D43.1 (K), D44.1 (K), D45.1 (K), D46.1 (K), D47.1 (K), D48.1 (K), D49.1 (K), D50.1 (K), J1.10
Row 3: D51.1 (K), D52.1 (K), D53.1 (K), D54.1 (K), D55.1 (K), D56.1 (K), D57.1 (K), D58.1 (K), D59.1 (K), D60.1 (K), D61.1 (K), D62.1 (K), D63.1 (K), J1.12
Row 4: D64.1 (K), D65.1 (K), D66.1 (K), D67.1 (K), D68.1 (K), D69.1 (K), D70.1 (K), D71.1 (K), D72.1 (K), D73.1 (K), D74.1 (K), D75.1 (K), D76.1 (K), D77.1 (K), J1.14
Row 5: D78.1 (K), D79.1 (K), D80.1 (K), D81.1 (K), D82.1 (K), D83.1 (K), D84.1 (K), D85.1 (K), D86.1 (K), D87.1 (K), D88.1 (K), J1.16
